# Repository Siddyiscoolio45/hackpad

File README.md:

After a lot of work, I present my macropad:

I wanted to create this macropad to speed up the work I do at my desk, and I mapped the macropad keys to my most used computer commands, like copy/paste, and undo/redo. 
I opted for a more unique design with more buttons and a rotary encoder for volume control. I also tried to add LEDs as a backlight so I can use the Macropad in the dark.

BOM:

* 6x CherryMX Switches
* 2x SK6812 MINI LEDs
* 1x Through-hole Xiao RP2040
* 6x Blank Keycaps
* 4x M3x16 Bolts
* 4x M3 heatset inserts

Other information:

| **Schematic** | **PCB** | **Case** |
|:-------------:|:-------:|:--------:|
|  |  |  |

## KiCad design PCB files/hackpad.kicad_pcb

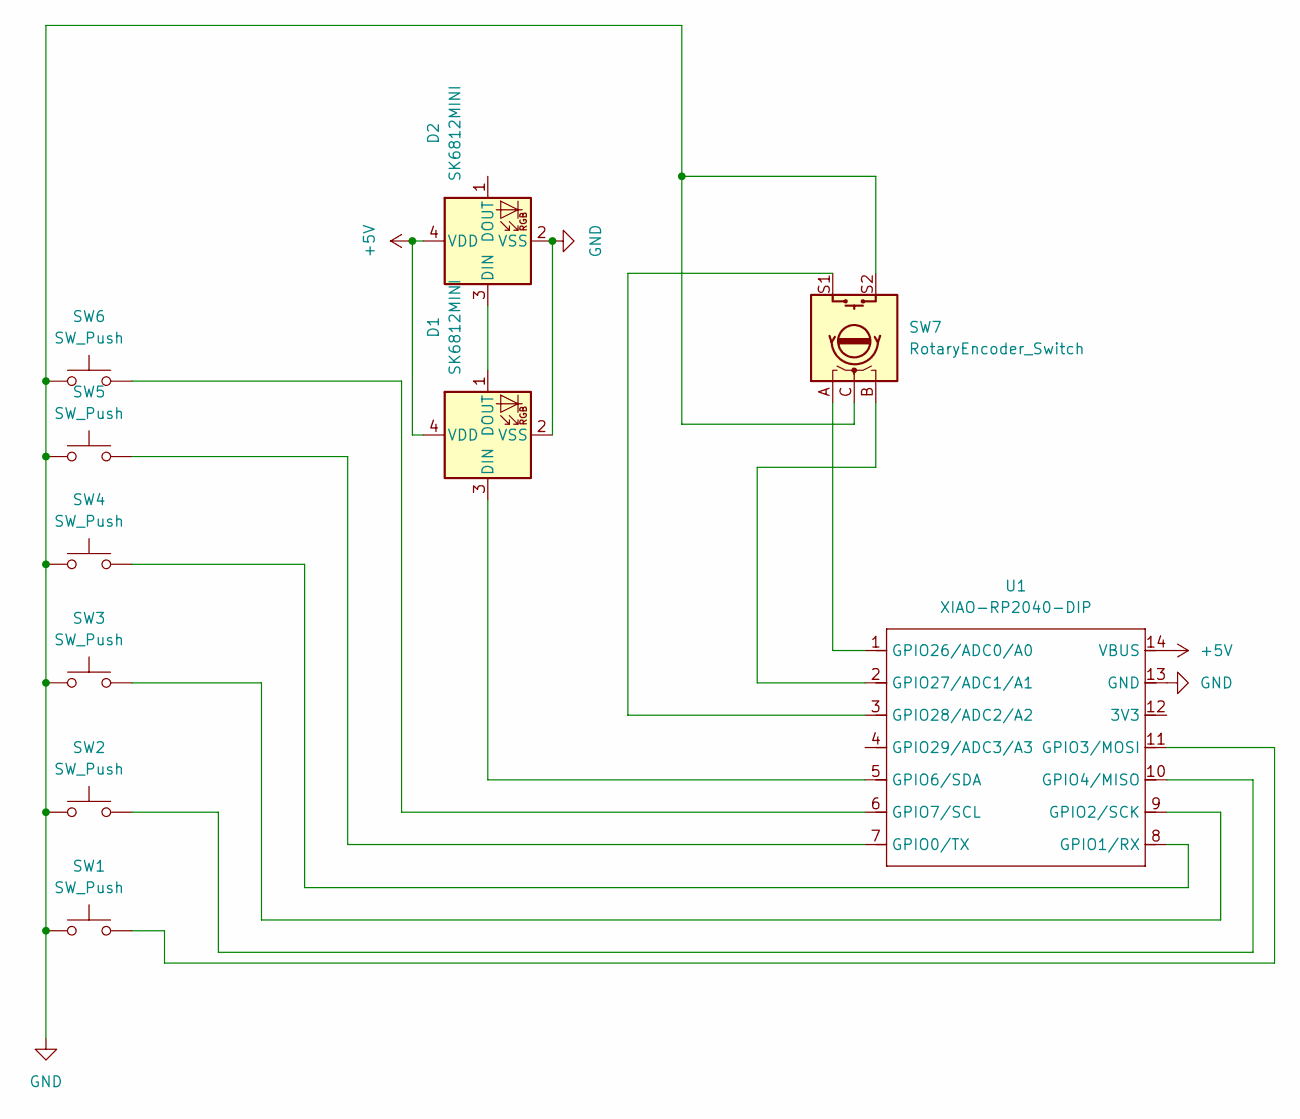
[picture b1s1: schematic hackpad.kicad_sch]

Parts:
D1, D2: SK6812MINI; LED_SK6812MINI_PLCC4_3.5x3.5mm_P1.75mm
SW1, SW2, SW3, SW4, SW5, SW6: SW_Push; SW_Cherry_MX_1.00u_PCB
SW7: RotaryEncoder_Switch; RotaryEncoder_Alps_EC11E-Switch_Vertical_H20mm
U1: XIAO-RP2040-DIP

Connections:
+5V: D1.4 (VDD), D2.4 (VDD), U1.14 (VBUS)
GND: D1.2 (VSS), D2.2 (VSS), SW1.1, SW2.1, SW3.1, SW4.1, SW5.1, SW6.1, SW7.C, SW7.S2, U1.13 (GND)
unnamed: D1.3 (DIN), U1.5 (GPIO6/SDA)
unnamed: D1.1 (DOUT), D2.3 (DIN)
unnamed: SW5.2, U1.7 (GPIO0/TX)
unnamed: SW4.2, U1.8 (GPIO1/RX)
unnamed: SW3.2, U1.9 (GPIO2/SCK)
unnamed: SW1.2, U1.11 (GPIO3/MOSI)
unnamed: SW2.2, U1.10 (GPIO4/MISO)
unnamed: SW6.2, U1.6 (GPIO7/SCL)
unnamed: SW7.A, U1.1 (GPIO26/ADC0/A0)
unnamed: SW7.B, U1.2 (GPIO27/ADC1/A1)
unnamed: SW7.S1, U1.3 (GPIO28/ADC2/A2)

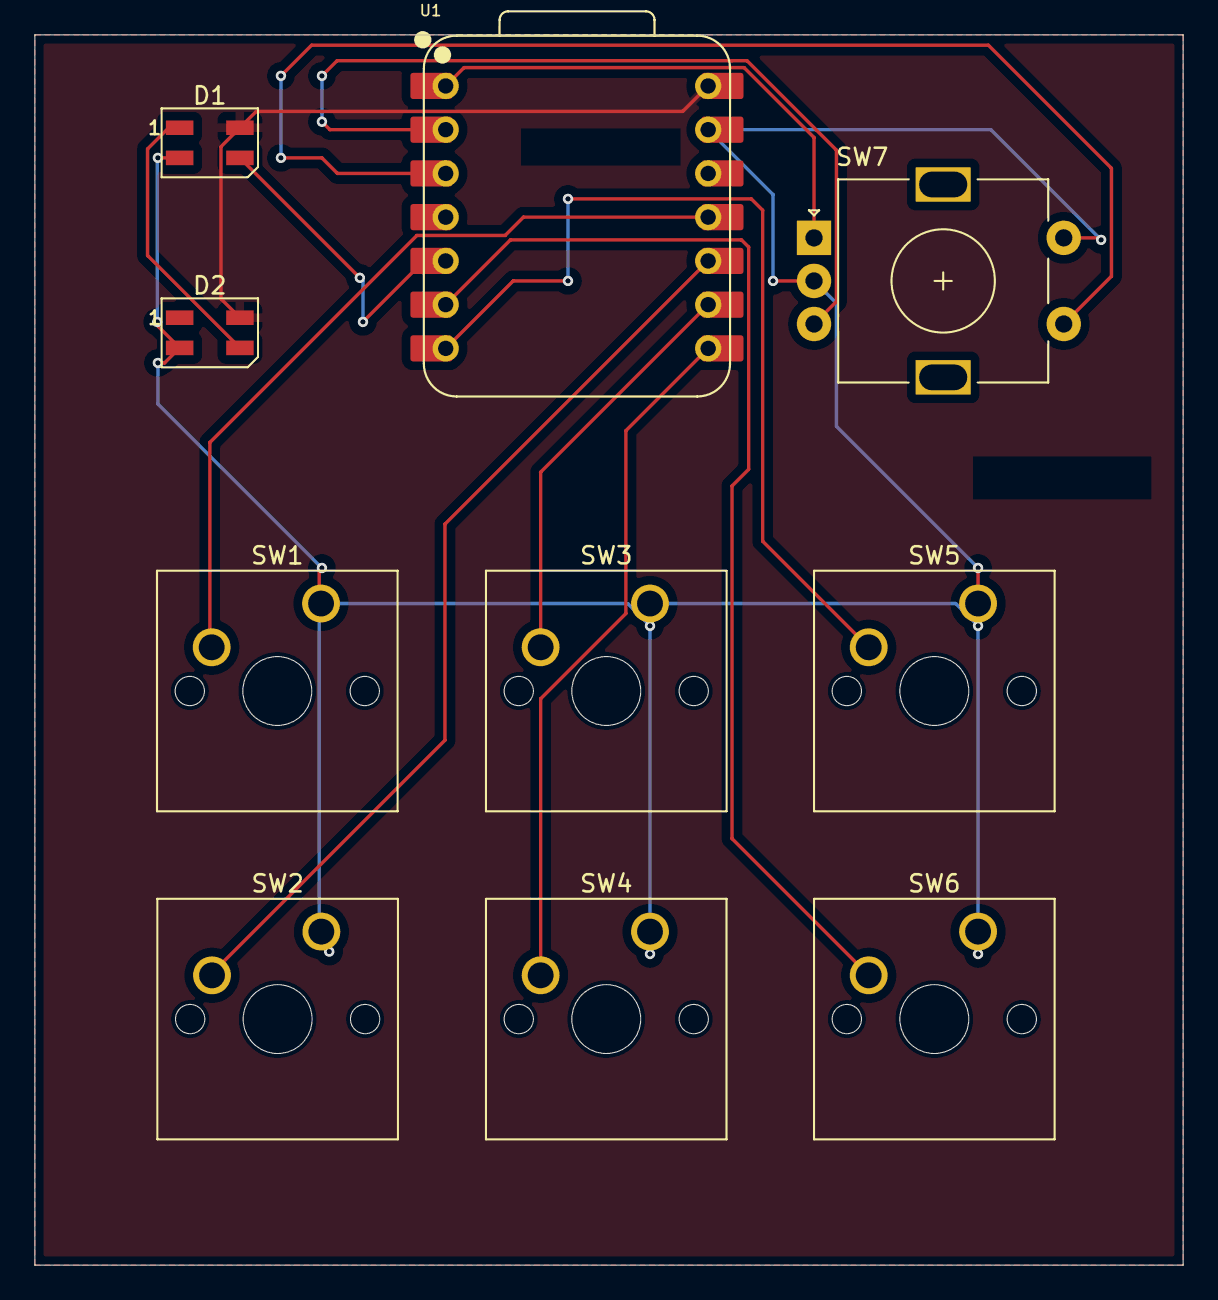
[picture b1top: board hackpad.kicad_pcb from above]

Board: 2 copper layers, 66.7 x 71.4 mm, 10 parts (0 on the bottom side), 13 nets.

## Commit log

2025-12-31 Add pcb files
2025-12-31 Full cad assembly
2025-12-31 Format files
2025-12-31 CAD files
2025-12-31 Add README
2025-12-31 Fix table formatting in README.md
2025-12-31 Improve image table formatting in README
2025-12-31 Refactor images in README for better display
